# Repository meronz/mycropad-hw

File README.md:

# Mycropad Hardware
Schematics and build files. Made with KiCAD and FreeCAD.

---
## Other Repos
- [Mycropad Firmware](https://github.com/meronz/mycropad-fw)
- [Mycropad Application](https://github.com/meronz/mycropad-app)

---
## Materials
These are the materials to buy if you want to build it. Buy links are here as an example, you can choose your own sources.

| Reference | Name |  Qty |  Value | Buy Link |
| :--- | :--- | :--- | :--- | :--- |
| C1 C2 C3 C4 C5 C6 C7 C8  | SMD Capacitor C1206 3216Metric | 8 | 10uF | https://it.aliexpress.com/item/4001345918046.html |
| D1 D2 D3 D4 D5 D6 D7 D8  | LEDS SK6812MINI-E PLCC4 3.5x3.5mm P1.75mm | 8 | NULL | https://www.aliexpress.com/item/1005002347411683.html |
| R1  | DIN0204 L3.6mm D1.6mm P7.62mm Horizontal | 1 | 200R | https://it.aliexpress.com/item/1005001489793822.html |
| R2  | DIN0204 L3.6mm D1.6mm P7.62mm Horizontal | 1 | 10k | https://it.aliexpress.com/item/1005001489793822.html |
| ROT1  | PEC12R-3225F-S0024 | 1 | NULL | https://www.digikey.it/it/products/detail/bourns-inc/PEC12R-3225F-S0024/4699267 |
| SW1 SW2 SW3 SW4 SW5 SW6 SW7 SW8  | KAILH MECHANICAL KEY SWITCHES - | 8 | NULL | https://www.adafruit.com/product/4952 |
| U1  | RASPBERRY PI PICO RP2040 BOARD | 1 | NULL | https://www.digikey.it/it/products/detail/raspberry-pi/SC0915/13624793 |
| U2  | SN74AHCT125N IC BUF NON-INVERT 5.5V 14DIP | 1 | NULL | https://www.digikey.it/it/products/detail/texas-instruments/SN74AHCT125N/375798 |
| NULL | CLEAR KEYCAPS FOR MX COMPATIBLE | 8 | NULL | https://www.adafruit.com/product/5068 |
| NULL | 30\*10MM Aluminium Alloy Potentiometer Knob Cap  | 1 | NULL | https://www.aliexpress.com/item/4001089749890.html |

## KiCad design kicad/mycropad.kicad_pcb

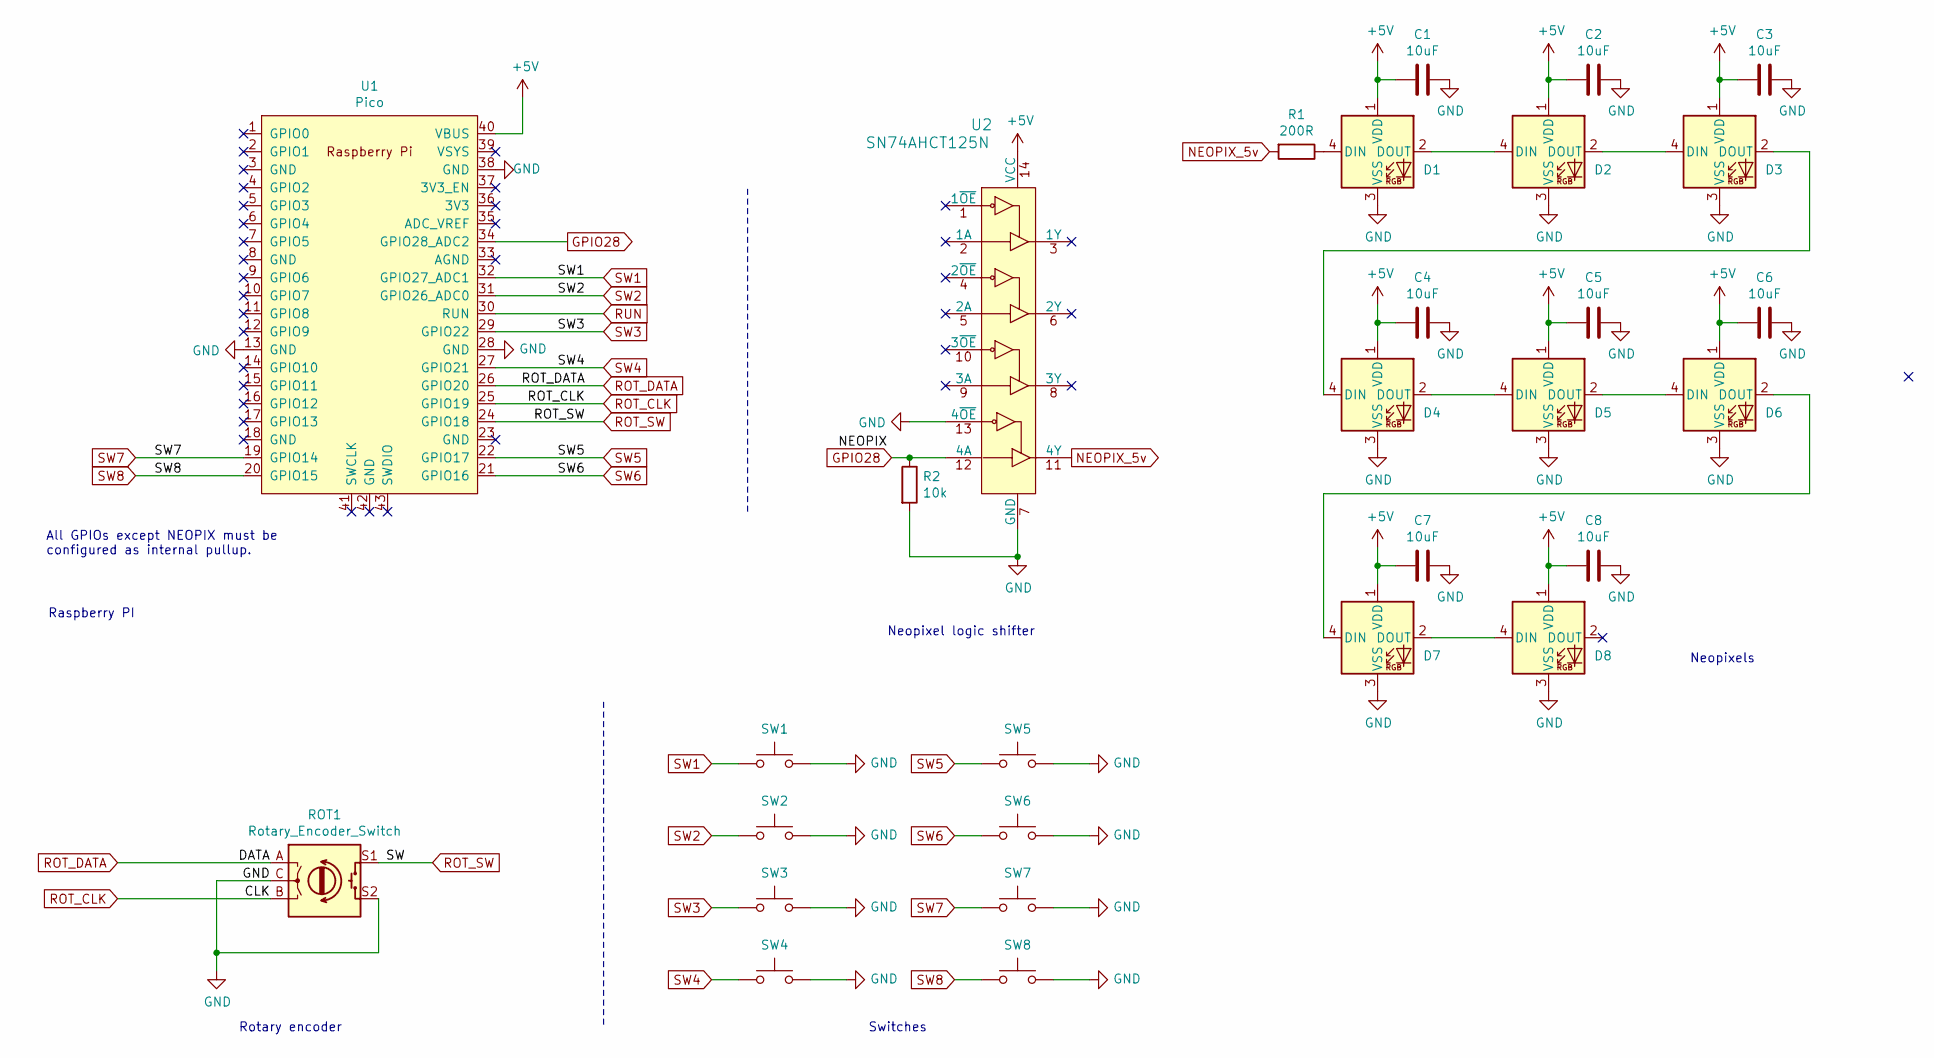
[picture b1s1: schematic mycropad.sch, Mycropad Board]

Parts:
C1, C2, C3, C4, C5, C6, C7, C8: 10uF; C_1206_3216Metric_Pad1.33x1.80mm_HandSolder; LCSC C13585
D1: SK6812MINI-E; LED_SK6812MINI-E_REV02_PLCC4_3.5x3.5mm_P1.75mm___V2; LCSC C13585
D2, D3, D4, D5, D6, D7, D8: SK6812MINI-E; LED_SK6812MINI-E_REV02_PLCC4_3.5x3.5mm_P1.75mm___V2
R1: 200R; R_Axial_DIN0204_L3.6mm_D1.6mm_P7.62mm_Horizontal
R2: 10k; R_Axial_DIN0204_L3.6mm_D1.6mm_P7.62mm_Horizontal
ROT1: Rotary_Encoder_Switch; RotaryEncoder_Alps_EC11E-Switch_Vertical_H20mm
SW1, SW2, SW3, SW4, SW5, SW6, SW7, SW8: SW_Push; SW_Cherry_MX_1.00u_PCB__Rotated
U1: Pico; RPi_Pico_SMD_TH
U2: SN74AHCT125N; DIP-14_W3mm; MPN SN74AHCT125N; Digi-Key_PN 296-4655-5-ND

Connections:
+5V: C1.2, C2.2, C3.2, C4.2, C5.2, C6.2, C7.2, C8.2, D1.1 (VDD), D2.1 (VDD), D3.1 (VDD), D4.1 (VDD), D5.1 (VDD), D6.1 (VDD), D7.1 (VDD), D8.1 (VDD), U1.40 (VBUS), U2.14 (VCC)
GND: C1.1, C2.1, C3.1, C4.1, C5.1, C6.1, C7.1, C8.1, D1.3 (VSS), D2.3 (VSS), D3.3 (VSS), D4.3 (VSS), D5.3 (VSS), D6.3 (VSS), D7.3 (VSS), D8.3 (VSS), R2.2, ROT1.C, ROT1.S2, SW1.2, SW2.2, SW3.2, SW4.2, SW5.2, SW6.2, SW7.2, SW8.2, U1.13 (GND), U1.28 (GND), U1.38 (GND), U2.7 (GND), U2.13 (4~OE)
GPIO28: R2.1, U1.34 (GPIO28_ADC2), U2.12 (4A)
NEOPIX_5v: R1.2, U2.11 (4Y)
unnamed: D1.2 (DOUT), D2.4 (DIN)
unnamed: D1.4 (DIN), R1.1
unnamed: D2.2 (DOUT), D3.4 (DIN)
unnamed: D3.2 (DOUT), D4.4 (DIN)
unnamed: D4.2 (DOUT), D5.4 (DIN)
unnamed: D5.2 (DOUT), D6.4 (DIN)
unnamed: D6.2 (DOUT), D7.4 (DIN)
unnamed: D7.2 (DOUT), D8.4 (DIN)
ROT_CLK: ROT1.B, U1.25 (GPIO19)
ROT_DATA: ROT1.A, U1.26 (GPIO20)
ROT_SW: ROT1.S1, U1.24 (GPIO18)
RUN: U1.30 (RUN)
SW1: SW1.1, U1.32 (GPIO27_ADC1)
SW2: SW2.1, U1.31 (GPIO26_ADC0)
SW3: SW3.1, U1.29 (GPIO22)
SW4: SW4.1, U1.27 (GPIO21)
SW5: SW5.1, U1.22 (GPIO17)
SW6: SW6.1, U1.21 (GPIO16)
SW7: SW7.1, U1.19 (GPIO14)
SW8: SW8.1, U1.20 (GPIO15)

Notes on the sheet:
Rotary encoder
Switches
Neopixel logic shifter
Neopixels
All GPIOs except NEOPIX must be configured as internal pullup.
Raspberry PI

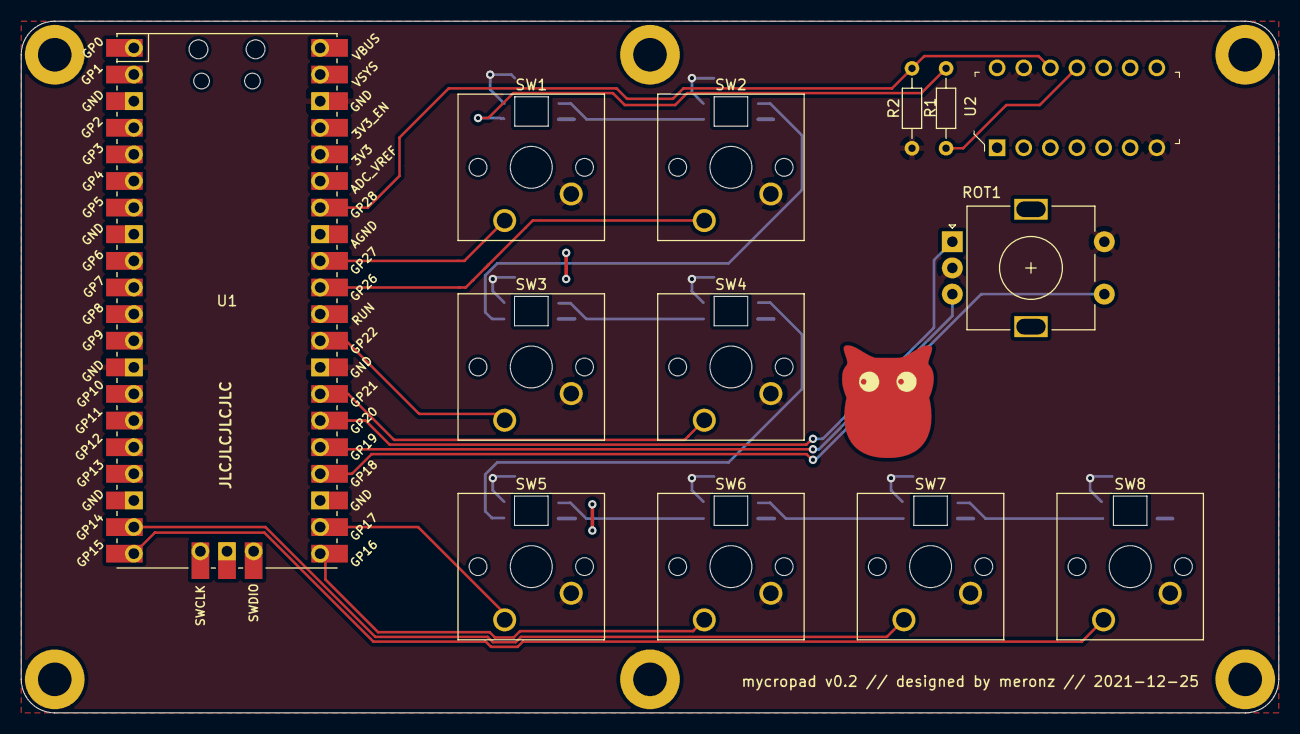
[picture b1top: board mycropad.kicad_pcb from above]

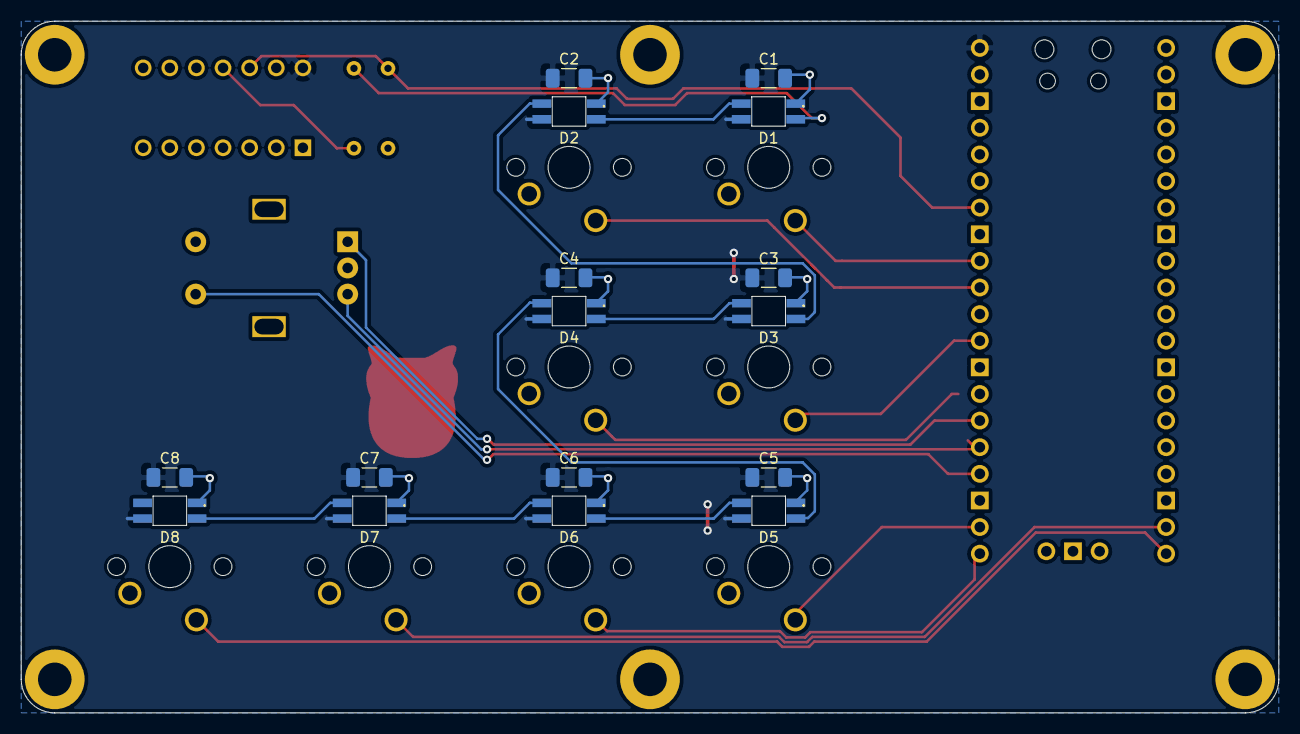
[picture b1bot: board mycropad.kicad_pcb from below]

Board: 2 copper layers, 120.0 x 66.0 mm, 36 parts (16 on the bottom side), 23 nets.

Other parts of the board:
M1, M2, M3, M4, M5, M6: MountingHole_3.2mm_M3_ISO7380_Pad
Ref**: Val**; owl_drawing

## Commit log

2021-10-07 WIP, first mockups
2021-10-07 Proper edges given
2021-10-07 Even better
2021-10-08 Added some 3d models
2021-10-09 Updated footprints
2021-10-09 Moved around some things
2021-10-30 Removed useless resistors, PCB design fixes.
2021-10-30 Added datasheets
2021-10-30 Restored original RPi SMD footprint
2021-10-30 Reinserted pcb mounting holes
2021-10-30 New reverse mount led. Let's hope it works...
2021-11-01 Updated footprints for SK6812 MINI-E.
2021-11-01 Adding FreeCAD project
2021-11-01 Completed top cover
2021-11-08 Added chamfer on the bottom to avoid elephant foot
2021-11-11 Enclosure fixes after the first printing test
2021-11-11 Addeed datasheet
2021-11-11 mycropad v0.2 started.
2021-11-11 mycropad v0.2 enclosure adjustments
2021-11-17 Changed board layout, r1 & r2 footprints, added reset button
2021-11-19 v0.2 enclosure, with new cover and inclined base
2021-11-19 New pcb holes layout
2021-11-27 Changed holes position
2021-11-27 Added owl art to pcb.
2021-11-27 Added production files for v02.
2021-11-27 Adapted holes to new pcb v0.2
2021-12-20 Edits before final print
2022-02-23 Added materials.
